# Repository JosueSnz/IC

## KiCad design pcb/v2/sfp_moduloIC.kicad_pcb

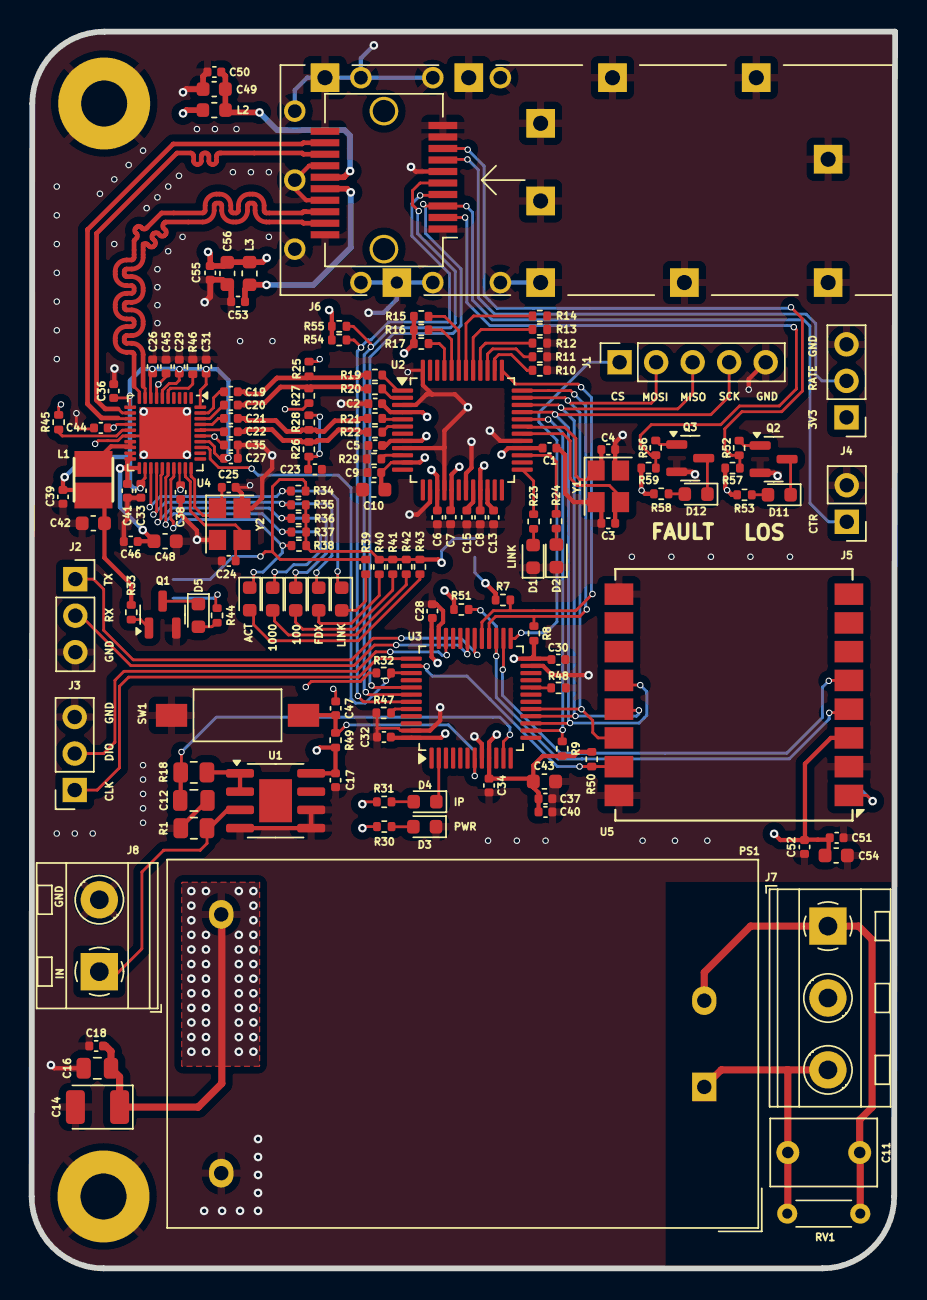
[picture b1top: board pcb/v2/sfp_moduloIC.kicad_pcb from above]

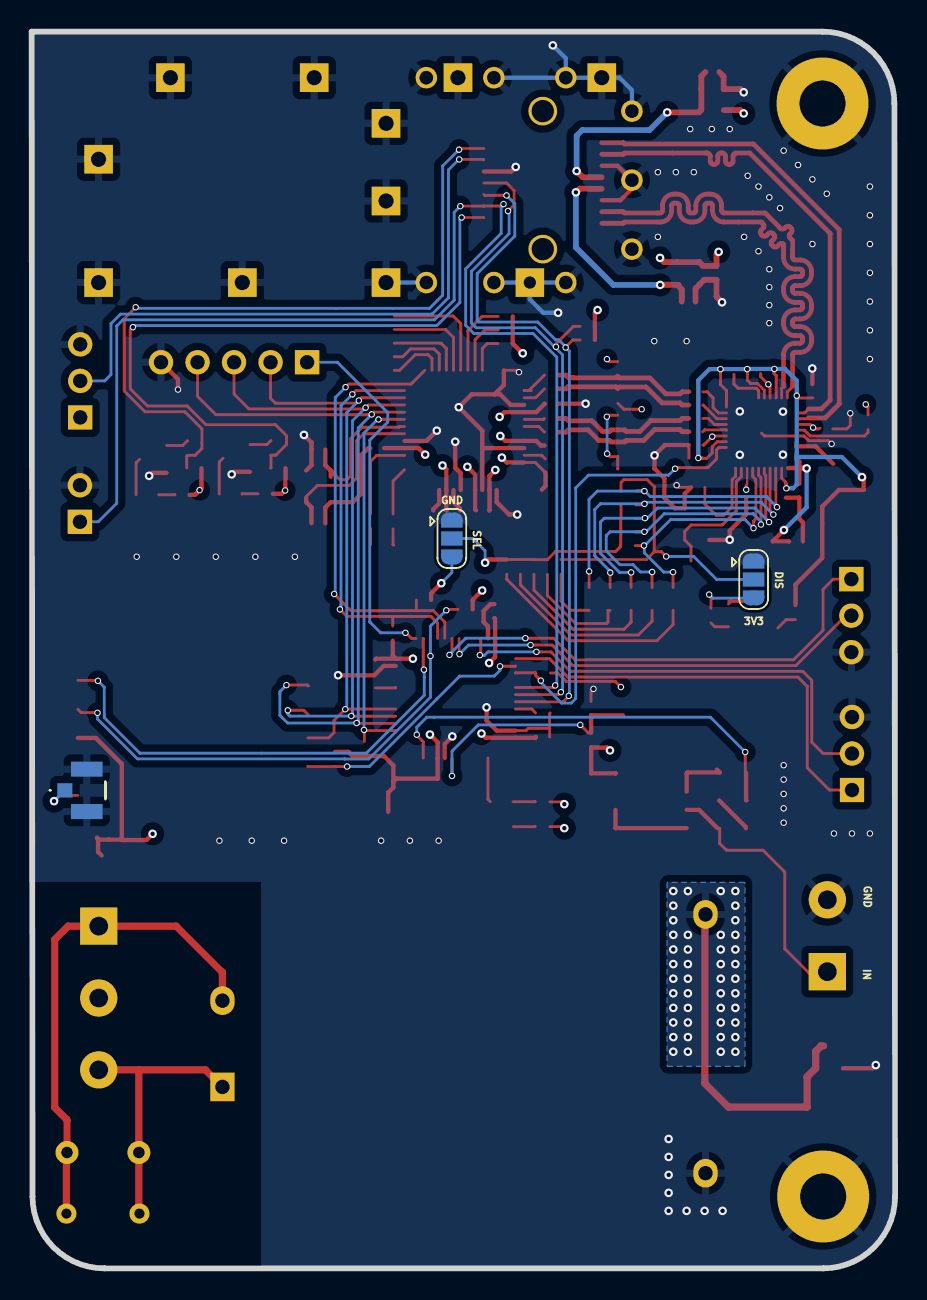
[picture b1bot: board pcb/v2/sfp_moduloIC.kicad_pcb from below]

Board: 4 copper layers, 60.1 x 86.0 mm, 151 parts (3 on the bottom side), 98 nets.

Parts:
C1, C2, C5, C6, C7, C8, C9, C17, C18, C26, C27, C28, C29, C30, C31, C32, C33, C34, C35, C36, C37, C38, C41, C44, C45, C47, C50, C51, C53, C55: 100n; C_0402_1005Metric
C3, C4, C24, C25: 15p; C_0402_1005Metric
C10, C42, C43, C48, C49, C56: 10u; C_0603_1608Metric
C11: 0,1u/225V; C_Rect_L7.2mm_W4.5mm_P5.00mm_FKS2_FKP2_MKS2_MKP2
C12: 100n; C_0805_2012Metric
C13, C19, C20, C21, C22, C23, C39, C40, C46, C52: 10n; C_0402_1005Metric
C14: 100u; CP_EIA-3528-21_Kemet-B
C15: 4,7u; C_0402_1005Metric
C16: 1u; C_0805_2012Metric
C54: 1u; C_0603_1608Metric
D1, D2, D3, D4, D5, D6, D7, D8, D9, D10, D11, D12: LED; LED_0603_1608Metric
H1, H2: FIX; MountingHole_3.2mm_M3_Pad
J1: SPI; PinSocket_1x05_P2.54mm_Vertical
J2: FTDI; PinSocket_1x03_P2.54mm_Vertical
J3: SWD; PinSocket_1x03_P2.54mm_Vertical
J4: RATE; PinHeader_1x03_P2.54mm_Vertical
J5: DIS; PinHeader_1x02_P2.54mm_Vertical
J6: SFP; Connector_SFP_and_Cage
J7: POWER; TerminalBlock_MetzConnect_Type094_RT03503HBLU_1x03_P5.00mm_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
J8: IN; TerminalBlock_MetzConnect_Type094_RT03502HBLU_1x02_P5.00mm_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
J11: ANT; CONUFL001SMDT
JP1, JP2: SEL; SolderJumper-3_P1.3mm_Open_RoundedPad1.0x1.5mm
L1: 2,2uH; INDPM3027X150L
L2, L3: 1nH; L_0603_1608Metric
PS1: HLK-5M03; Converter_ACDC_Hi-Link_HLK-5Mxx
Q1, Q2, Q3: BC848; SOT-23
R1: 100R 1%; R_0805_2012Metric
R7, R8, R9, R10, R11, R12, R13, R14, R15, R16, R17, R32, R50, R51, R52, R54, R55, R56, R57, R59: 10k; R_0402_1005Metric
R18: 10k; R_0805_2012Metric
R19, R20, R21, R22: 33R; R_0402_1005Metric
R23, R24, R30, R31, R33, R39, R40, R41, R42, R43, R44, R53, R58: 1k; R_0402_1005Metric
R25, R26, R27, R28: 49R9 1%; R_0402_1005Metric
R29: 12,4k 1%; R_0402_1005Metric
R34, R35, R36, R37, R38, R45, R47, R48, R49: 4,7k; R_0402_1005Metric
R46: 2,5k 1%; R_0402_1005Metric
RV1: 10D561K; R_Axial_DIN0204_L3.6mm_D1.6mm_P5.08mm_Horizontal
SW1: RESET; SW_SPST_FSMSM
U1: MCP6002-xSN; SOIC-8-1EP_3.9x4.9mm_P1.27mm_EP2.29x3mm
U2: W5500; LQFP-48_7x7mm_P0.5mm
U3: STM32F103C8Tx; LQFP-48_7x7mm_P0.5mm
U4: RTL8213B-CG; QFN-40-1EP_5x5mm_P0.4mm_EP3.6x3.6mm
U5: Ai-Thinker-Ra-01; Ai-Thinker-Ra-01-LoRa
Y1, Y2: 25mhz; Crystal_SMD_3225-4Pin_3.2x2.5mm

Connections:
+1V0: C26.1, C27.1, C29.1, C31.1, C33.1, C36.1, C39.1, C42.1, L1.1, R33.1, U4.6 (AVDDL), U4.8 (DVDDL), U4.11 (SVDDL), U4.22 (DVDDL), U4.34 (PLLVDDL), U4.40 (AVDDL)
+3V3: C1.1, C2.1, C5.1, C6.1, C7.1, C8.1, C9.1, C10.1, C14.1, C16.1, C17.1, C18.1, C28.1, C30.1, C32.1, C34.1, C35.1, C37.1, C38.1, C40.1, C41.1, C43.1, C44.1, C45.1, C46.1, C48.1, C51.1, C52.1, C54.1, C55.1, C56.1, J4.1, JP1.3 (B), JP2.3 (B), L2.2, L3.2, PS1.4 (+Vout), R7.2, R8.2, R9.2, R15.2, R16.2, R17.2, R25.2, R27.2, R30.2, R31.2, R32.2, R44.2, R45.1, R49.2, R50.2, R51.2, R53.2, R54.2, R55.2, R57.2, R58.2, R59.2, U1.8 (V+), U2.4 (AVDD), U2.8 (AVDD), U2.11 (AVDD), U2.15 (AVDD), U2.17 (AVDD), U2.21 (AVDD), U2.28 (VDD), U3.9 (VDDA), U3.24 (VDD), U3.36 (VDD), U3.48 (VDD), U4.7 (AVDDH), U4.14 (AVDDH), U4.19 (HV_SWR), U4.20 (HV_SWR), U4.21 (DVDDIO), U4.28 (AVDDH), U4.35 (AVDDH), U5.3 (VDD)
/ANT: J11.1 (In), U5.1 (ANT)
/BOOT0: R47.1, U3.44 (BOOT0)
/BOOT1: R48.1, U3.20 (PB2)
/CONFIG: JP2.2 (C), R35.1, R36.1, R37.1, R38.1, R40.1, R41.1, R42.1, R43.1
/CS1: R9.1, U2.32 (~SCS), U3.14 (PA4)
/CS2: R50.1, U3.38 (PA15), U5.15 (~NSS)
/CS3: J1.1, U3.25 (PB12)
/CTRL: J5.1, J6.3 (TX_DISABLE), U3.41 (PB5)
/DISAUTO: JP1.2 (C), R34.1, R39.1
/FAULT: J6.2 (TX_FAULT), R56.2, R59.1
/HSI+: J6.13 (RD+), U4.12 (HSIP)
/HSI-: J6.12 (RD-), U4.13 (HSIN)
/HSO+: J6.18 (TD+), U4.10 (HSOP)
/HSO-: J6.19 (TD-), U4.9 (HSON)
/IN: J8.1, R1.1, U1.3 (+)
/INT1: R8.1, U2.36 (~INT), U3.28 (PB15)
/INT2: U3.26 (PB13), U5.5 (DIO0)
/L: C11.1, J7.3, PS1.1 (AC/L), RV1.1
/LOS: J6.8 (RX_LOS), R52.2, R57.1
/MISO: J1.3, U2.34 (MISO), U3.16 (PA6), U5.13 (MISO)
/MOSI: J1.2, U2.35 (MOSI), U3.17 (PA7), U5.14 (MOSI)
/N: C11.2, J7.1, PS1.2 (AC/N), RV1.2
/OUT: C12.1, R18.1, U3.11 (PA1)
/R+: C22.2, R22.2, R26.2
/R-: C21.2, R21.2, R28.2
/RC: C23.1, R26.1, R28.1
/RD+: C22.1, U4.36 (P3MDIAP)
/RD-: C21.1, U4.37 (P3MDIAN)
/RESET: C47.1, R49.1, SW1.2 (B), U3.7 (NRST)
/RST1: R7.1, U2.37 (~RST), U3.29 (PA8)
/RST2: R51.1, U3.27 (PB14), U5.4 (~RESET)
/RST3: R32.1, U3.39 (PB3), U4.33 (nRESET)
/RX1: J2.2, U3.31 (PA10)
/SCK: J1.4, U2.33 (SCLK), U3.15 (PA5), U5.12 (SCK)
/SCL: J6.5 (MOD_DEF1), R55.1, U3.42 (PB6)
/SDA: J6.4 (MOD_DEF2), R54.1, U3.43 (PB7)
/SWCLK: J3.1, U3.37 (PA14)
/SWDIO: J3.2, U3.34 (PA13)
/T+: C20.2, R20.2, R27.1
/T-: C19.2, R19.2, R25.1
/TD+: C20.1, U4.38 (P3MDIBP)
/TD-: C19.1, U4.39 (P3MDIBN)
/TX1: J2.1, U3.30 (PA9)
/VccR: C49.1, C50.1, J6.15 (VccR), L2.1
/VccT: C53.1, J6.16 (VccT), L3.1
GND: C1.2, C2.2, C3.1, C4.1, C5.2, C6.2, C7.2, C8.2, C9.2, C10.2, C12.2, C13.2, C14.2, C15.2, C16.2, C17.2, C18.2, C23.2, C24.1, C25.1, C26.2, C27.2, C28.2, C29.2, C30.2, C31.2, C32.2, C33.2, C34.2, C35.2, C36.2, C37.2, C38.2, C39.2, C40.2, C41.2, C42.2, C43.2, C44.2, C45.2, C46.2, C47.2, C48.2, C49.2, C50.2, C51.2, C52.2, C53.2, C54.2, C55.2, C56.2, D1.1 (K), D2.1 (K), D3.1 (K), H1.1, H2.1, J1.5, J2.3, J3.3, J4.3, J5.2, J6.1 (VeeT), J6.6 (MOD_DEF0), J6.9 (VeeR), J6.10 (VeeR), J6.11 (VeeR), J6.14 (VeeR), J6.17 (VeeT), J6.20 (VeeT), J6.CAGE, J8.2, J11.2 (Ext), J11.3 (arm), JP1.1 (A), JP2.1 (A), PS1.3 (-Vout), Q1.2 (E), Q2.2 (E), Q3.2 (E), R1.2, R10.2, R11.2, R12.2, R13.2, R14.2, R29.1, R46.2, R47.2, R48.2, SW1.1 (A), U1.4 (V-), U1.5 (+), U1.6 (-), U2.3 (AGND), U2.9 (AGND), U2.14 (AGND), U2.16 (AGND), U2.19 (AGND), U2.29 (GND), U2.48 (AGND), U3.8 (VSSA), U3.23 (VSS), U3.35 (VSS), U3.47 (VSS), U4.16 (GND_SWR), U4.41 (EGND), U5.2 (GND), U5.9 (GND), U5.16 (GND), Y1.2, Y1.4, Y2.2, Y2.4
unnamed: D1.2 (A), R23.2
unnamed: D2.2 (A), R24.2
unnamed: D3.2 (A), R30.1
unnamed: D4.2 (A), R31.1
unnamed: D4.1 (K), U3.2 (PC13)
unnamed: D5.2 (A), R44.1
unnamed: D5.1 (K), Q1.3 (C)
unnamed: D6.2 (A), R39.2
unnamed: D6.1 (K), R34.2, U4.23 (P6LED1)
unnamed: D7.2 (A), R40.2
unnamed: D7.1 (K), R35.2, U4.24 (P6LED0)
unnamed: D8.2 (A), R41.2
unnamed: D8.1 (K), R36.2, U4.25 (P3LED2)
unnamed: D9.2 (A), R42.2
unnamed: D9.1 (K), R37.2, U4.26 (P3LED1)
unnamed: D10.2 (A), R43.2
unnamed: D10.1 (K), R38.2, U4.27 (P3LED0)
unnamed: D11.2 (A), R53.1
unnamed: D11.1 (K), Q2.3 (C)
unnamed: D12.2 (A), R58.1
unnamed: D12.1 (K), Q3.3 (C)
unnamed: J4.2, J6.7 (RATE_SELECT)
unnamed: L1.2, U4.17 (LX), U4.18 (LX)
unnamed: Q1.1 (B), R33.2
unnamed: Q2.1 (B), R52.1
unnamed: Q3.1 (B), R56.1
unnamed: R10.1, U2.38 (RSVD)
unnamed: R11.1, U2.39 (RSVD)
unnamed: R12.1, U2.40 (RSVD)
unnamed: R13.1, U2.41 (RSVD)
unnamed: R14.1, U2.42 (RSVD)
unnamed: R18.2, U1.1, U1.2 (-)
unnamed: C13.1, U2.22 (1V2O)
unnamed: R24.1, U2.27 (ACTLED)
unnamed: R29.2, U2.10 (EXRES1)
unnamed: R23.1, U2.25 (LINKLED)
unnamed: R17.1, U2.45 (PMODE0)
unnamed: R16.1, U2.44 (PMODE1)
unnamed: R15.1, U2.43 (PMODE2)
unnamed: R21.1, U2.5 (RXN)
unnamed: R22.1, U2.6 (RXP)
unnamed: C15.1, U2.20 (TOCAP)
unnamed: R19.1, U2.1 (TXN)
unnamed: R20.1, U2.2 (TXP)
unnamed: C3.2, U2.30 (XI/CLKIN), Y1.3
unnamed: C4.2, U2.31 (XO), Y1.1
unnamed: R45.2, U4.15 (EN_SWR)
unnamed: R46.1, U4.5 (MDIREF)
unnamed: C25.2, U4.30 (XTALI), Y2.1
unnamed: C24.2, U4.29 (XTALO), Y2.3

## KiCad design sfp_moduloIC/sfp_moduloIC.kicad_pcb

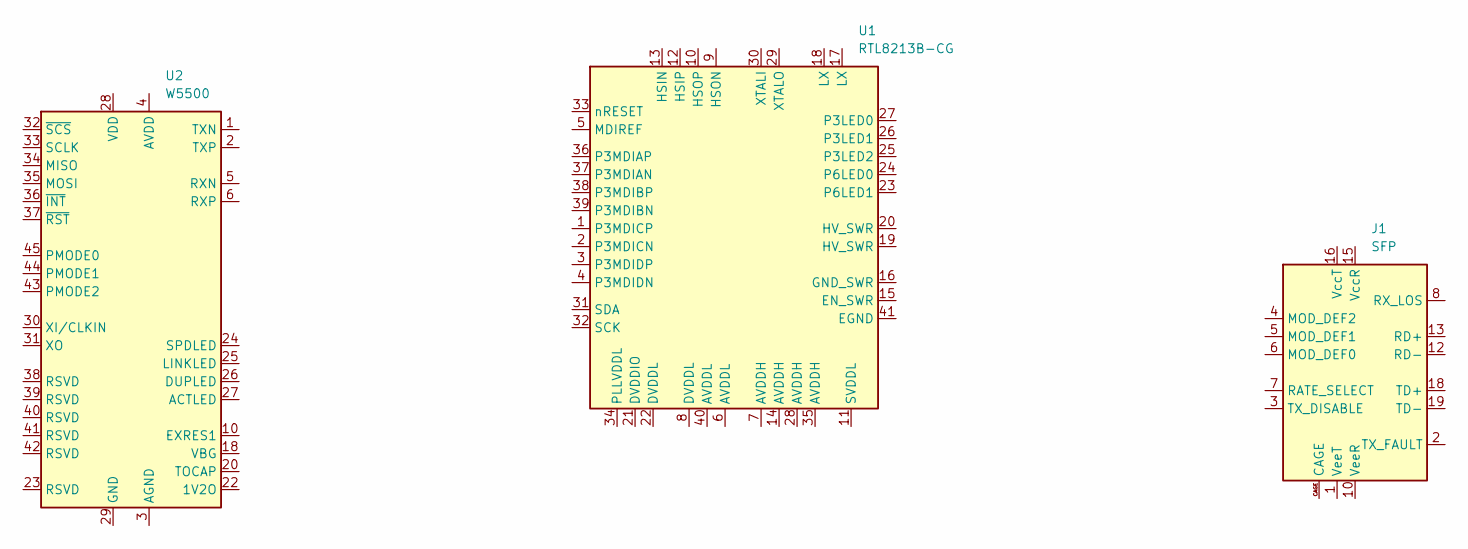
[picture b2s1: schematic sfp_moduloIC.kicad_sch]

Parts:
J1: SFP; Connector_SFP_and_Cage
U1: RTL8213B-CG; QFN-40-1EP_5x5mm_P0.4mm_EP3.8x3.8mm_ThermalVias
U2: W5500; LQFP-48_7x7mm_P0.5mm

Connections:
unnamed: J1.9 (VeeR), J1.10 (VeeR), J1.11 (VeeR), J1.14 (VeeR)
unnamed: J1.1 (VeeT), J1.17 (VeeT), J1.20 (VeeT)
unnamed: U2.3 (AGND), U2.9 (AGND), U2.14 (AGND), U2.16 (AGND), U2.19 (AGND), U2.48 (AGND)
unnamed: U2.4 (AVDD), U2.8 (AVDD), U2.11 (AVDD), U2.15 (AVDD), U2.17 (AVDD), U2.21 (AVDD)

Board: 2 copper layers, 3 parts (0 on the bottom side), 4 nets, no tracks yet.

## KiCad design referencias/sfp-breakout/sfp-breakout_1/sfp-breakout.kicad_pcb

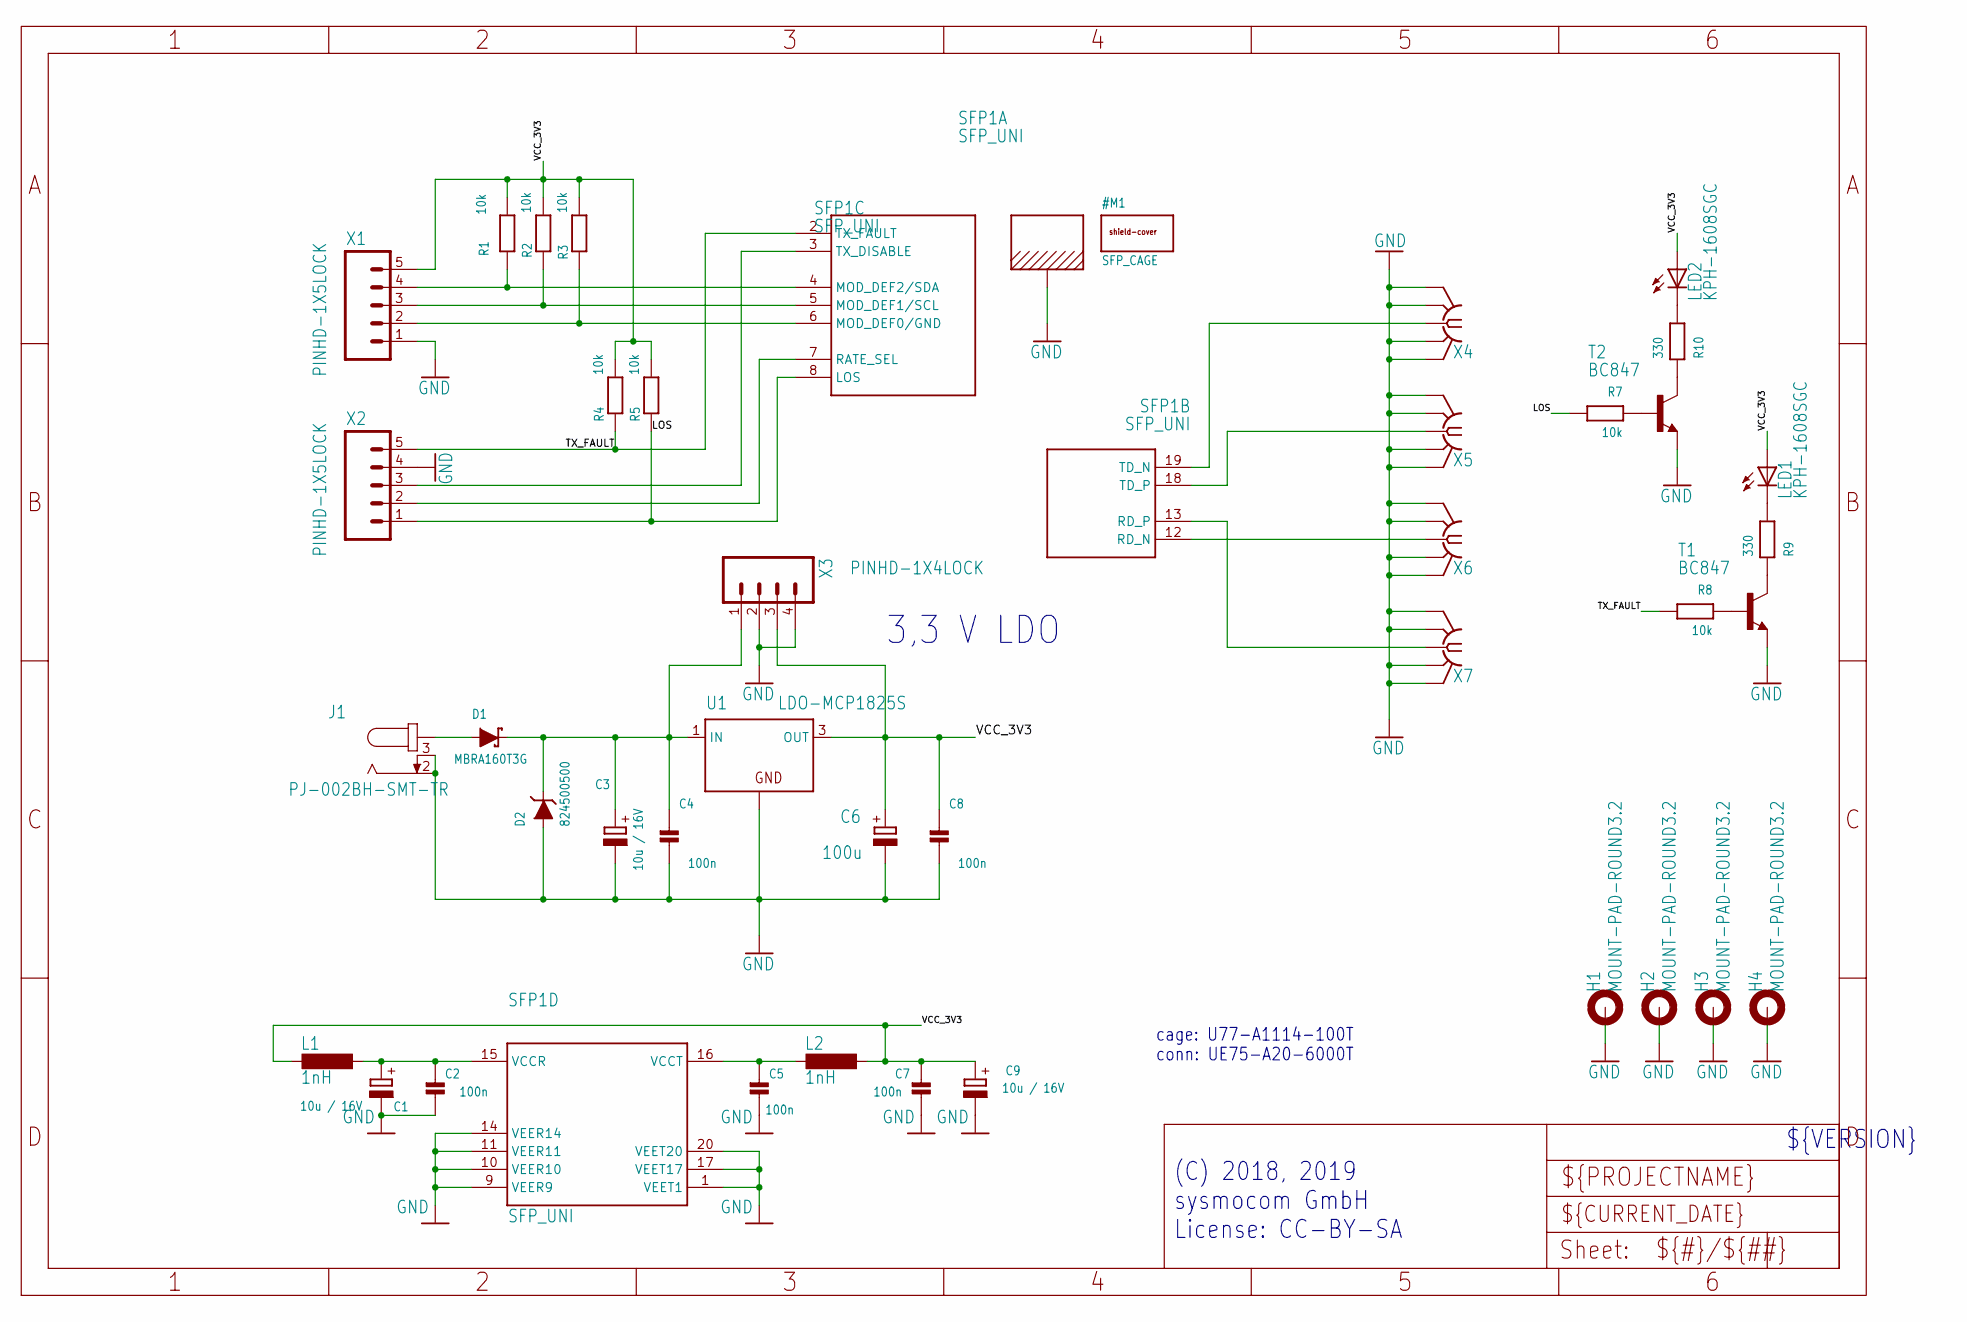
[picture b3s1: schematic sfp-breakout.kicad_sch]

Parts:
C1, C3, C9: 10u / 16V; CPOL1206; MANUFACTURERPARTNUMBER CL31A106KOHNNNE
C2, C4, C5, C7, C8: 100n; _0603; MANUFACTURERPARTNUMBER CL10B104KO8NNNC
C6: 100u; CT6032; MANUFACTURERPARTNUMBER TPSC107K006R0150
D1: MBRA160T3G; SMADIODE; MANUFACTURERPARTNUMBER B260A-13-F
D2: 824500500; SMADIODE; MANUFACTURERPARTNUMBER 824500500
H1, H2, H3, H4: MOUNT-PAD-ROUND3.2; 3,2-PAD; MANUFACTURERPARTNUMBER UNKNOWN MANUFACTURER PART NUMBER
J1: PJ-002BH-SMT-TR; 694108106102; MANUFACTURERPARTNUMBER PJ-002BH-SMT-TR
L1, L2: 1nH; 0603; MANUFACTURERPARTNUMBER AIMC-0603-1N0S-T
LED1, LED2: KPH-1608SGC; CHIP-LED0603; MANUFACTURERPARTNUMBER UNKNOWN MANUFACTURER PART NUMBER
R1, R2, R3, R4, R5, R7, R8: 10k; _0603; MANUFACTURERPARTNUMBER RMCF0603FT10K0
R9, R10: 330; _0603; MANUFACTURERPARTNUMBER RC0603FR-07330RL
SFP1: SFP_UNI; SFP_COMBINED; MANUFACTURERPARTNUMBER UE75-A20-6000T
T1, T2: BC847; SOT23-BEC; MANUFACTURERPARTNUMBER BC847C,215
U1: LDO-MCP1825S; SOT223; MANUFACTURERPARTNUMBER MCP1825ST-3302E/DB
X1, X2: PINHD-1X5LOCK; 1X05_LOCK; MANUFACTURERPARTNUMBER UNKNOWN MANUFACTURER PART NUMBER
X3: PINHD-1X4LOCK; 1X04_LOCK; MANUFACTURERPARTNUMBER UNKNOWN MANUFACTURER PART NUMBER
X4, X5, X6, X7: SMA-F-S-EDGE; MANUFACTURERPARTNUMBER UNKNOWN MANUFACTURER PART NUMBER

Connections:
+VIN: C3.+, C4.1, D1.C, D2.C, U1.1 (IN), X3.1
GND: C1.-, C2.2, C3.-, C4.2, C5.2, C6.-, C7.2, C8.2, C9.-, D2.A, H1.B3,2, H2.B3,2, H3.B3,2, H4.B3,2, J1.2, J1.3, SFP1.1 (VEET1), SFP1.9 (VEER9), SFP1.10 (VEER10), SFP1.11 (VEER11), SFP1.14 (VEER14), SFP1.17 (VEET17), SFP1.20 (VEET20), SFP1.A1 (CAGE), SFP1.A2 (CAGE), SFP1.A3 (CAGE), SFP1.A4 (CAGE), SFP1.A5 (CAGE), SFP1.A6 (CAGE), SFP1.A7 (CAGE), SFP1.A8 (CAGE), SFP1.A10 (CAGE), SFP1.A11 (CAGE), SFP1.A12 (CAGE), SFP1.B1 (CAGE), SFP1.B2 (CAGE), SFP1.B3 (CAGE), SFP1.B4 (CAGE), SFP1.B5 (CAGE), SFP1.B6 (CAGE), SFP1.B7 (CAGE), SFP1.B8 (CAGE), SFP1.B10 (CAGE), T1.E, T2.E, U1.2 (GND), U1.4 (GND), X1.1, X2.4, X3.2, X3.4, X4.BG1 (GND@1), X4.BG2 (GND@4), X4.TG1 (GND@2), X4.TG2 (GND@3), X5.BG1 (GND@1), X5.BG2 (GND@4), X5.TG1 (GND@2), X5.TG2 (GND@3), X6.BG1 (GND@1), X6.BG2 (GND@4), X6.TG1 (GND@2), X6.TG2 (GND@3), X7.BG1 (GND@1), X7.BG2 (GND@4), X7.TG1 (GND@2), X7.TG2 (GND@3)
LOS: R5.1, R7.2, SFP1.8 (LOS), X2.1
MOD_DEF0/GND: R3.1, SFP1.6 (MOD_DEF0/GND), X1.2
MOD_DEF1/SCL: R2.1, SFP1.5 (MOD_DEF1/SCL), X1.3
MOD_DEF2/SDA: R1.1, SFP1.4 (MOD_DEF2/SDA), X1.4
unnamed: D1.A, J1.1, J1.1-1 (1)
unnamed: R7.1, T2.B
unnamed: LED2.C, R10.2
unnamed: C5.1, L2.2, SFP1.16 (VCCT)
unnamed: C1.+, C2.1, L1.1, SFP1.15 (VCCR)
unnamed: R10.1, T2.C
unnamed: R8.1, T1.B
unnamed: LED1.C, R9.2
unnamed: R9.1, T1.C
RATE_SEL: SFP1.7 (RATE_SEL), X2.2
RD_N: SFP1.12 (RD_N), X6.C (1)
RD_P: SFP1.13 (RD_P), X7.C (1)
TD_N: SFP1.19 (TD_N), X4.C (1)
TD_P: SFP1.18 (TD_P), X5.C (1)
TX_DISABLE: SFP1.3 (TX_DISABLE), X2.3
TX_FAULT: R4.1, R8.2, SFP1.2 (TX_FAULT), X2.5
VCC_3V3: C6.+, C7.1, C8.1, C9.+, L1.2, L2.1, LED1.A, LED2.A, R1.2, R2.2, R3.2, R4.2, R5.2, U1.3 (OUT), X1.5, X3.3

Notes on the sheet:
conn: UE75-A20-6000T
(C) 2018, 2019 sysmocom GmbH License: CC-BY-SA
3,3 V LDO
${VERSION}
cage: U77-A1114-100T

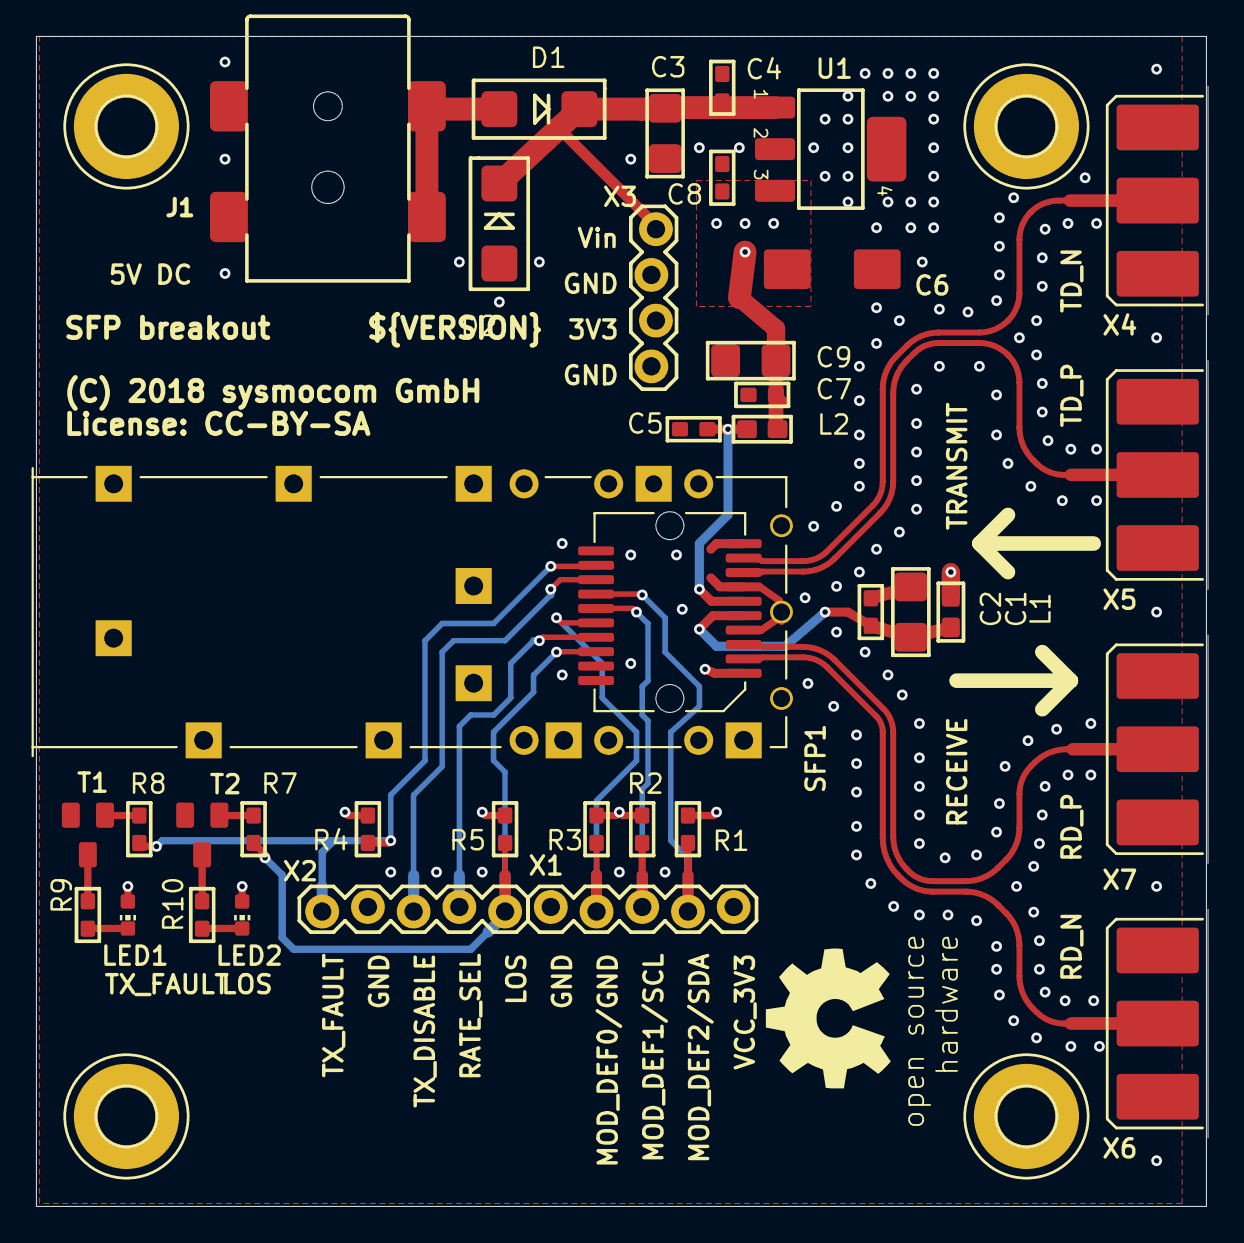
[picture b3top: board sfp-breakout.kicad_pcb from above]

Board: 4 copper layers, 65.0 x 65.0 mm, 41 parts (0 on the bottom side), 23 nets.

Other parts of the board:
U$1: OSHW_8MM

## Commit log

2025-10-20 v2.1
2025-11-11 v4.1

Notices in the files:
referencias/sfp-breakout/sfp-breakout_1/sfp-breakout.kicad_pcb:
(C) 2018 sysmocom GmbH
License: CC-BY-SA
